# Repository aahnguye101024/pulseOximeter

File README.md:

# pulseOximeter
This board attempts to use the MAX86150 to in a small board to receive PPG, EKG, SPO2, and Heart Rate information. It features an nrf52832, some basic ui leds, and a power system capable of running off of and charging a lipo battery

# Board Pictures

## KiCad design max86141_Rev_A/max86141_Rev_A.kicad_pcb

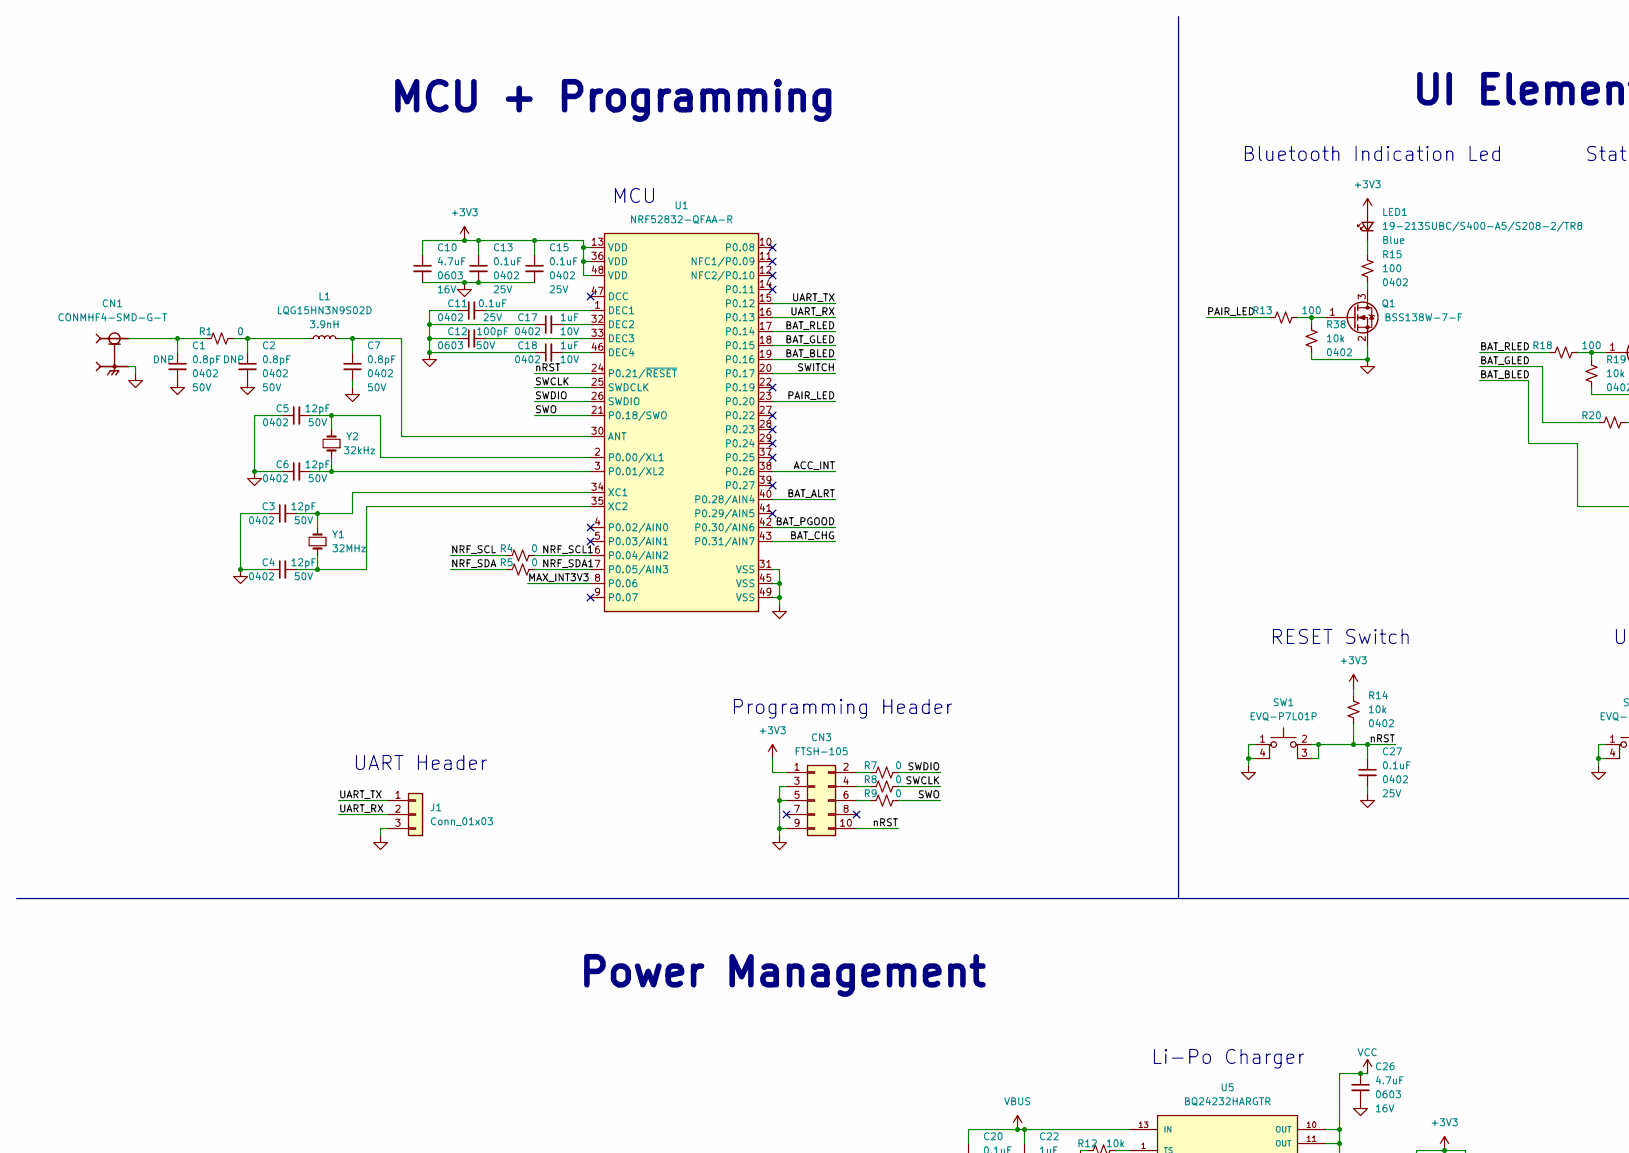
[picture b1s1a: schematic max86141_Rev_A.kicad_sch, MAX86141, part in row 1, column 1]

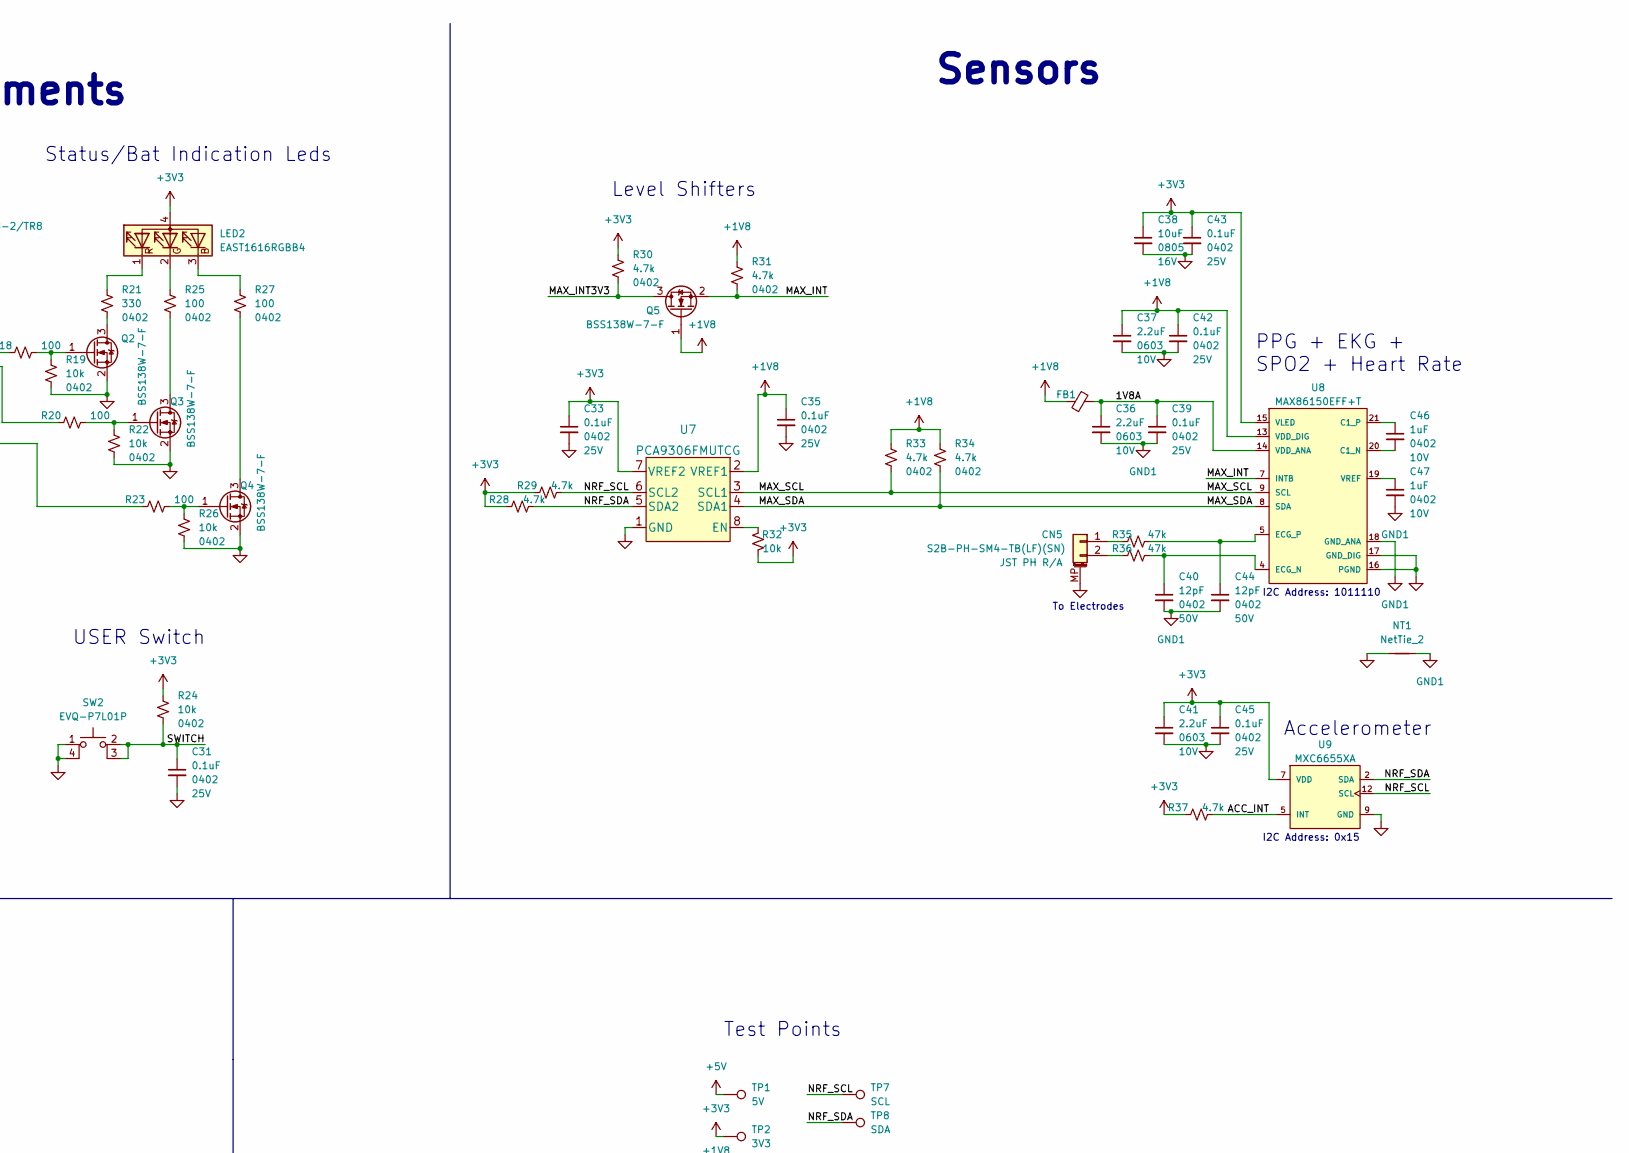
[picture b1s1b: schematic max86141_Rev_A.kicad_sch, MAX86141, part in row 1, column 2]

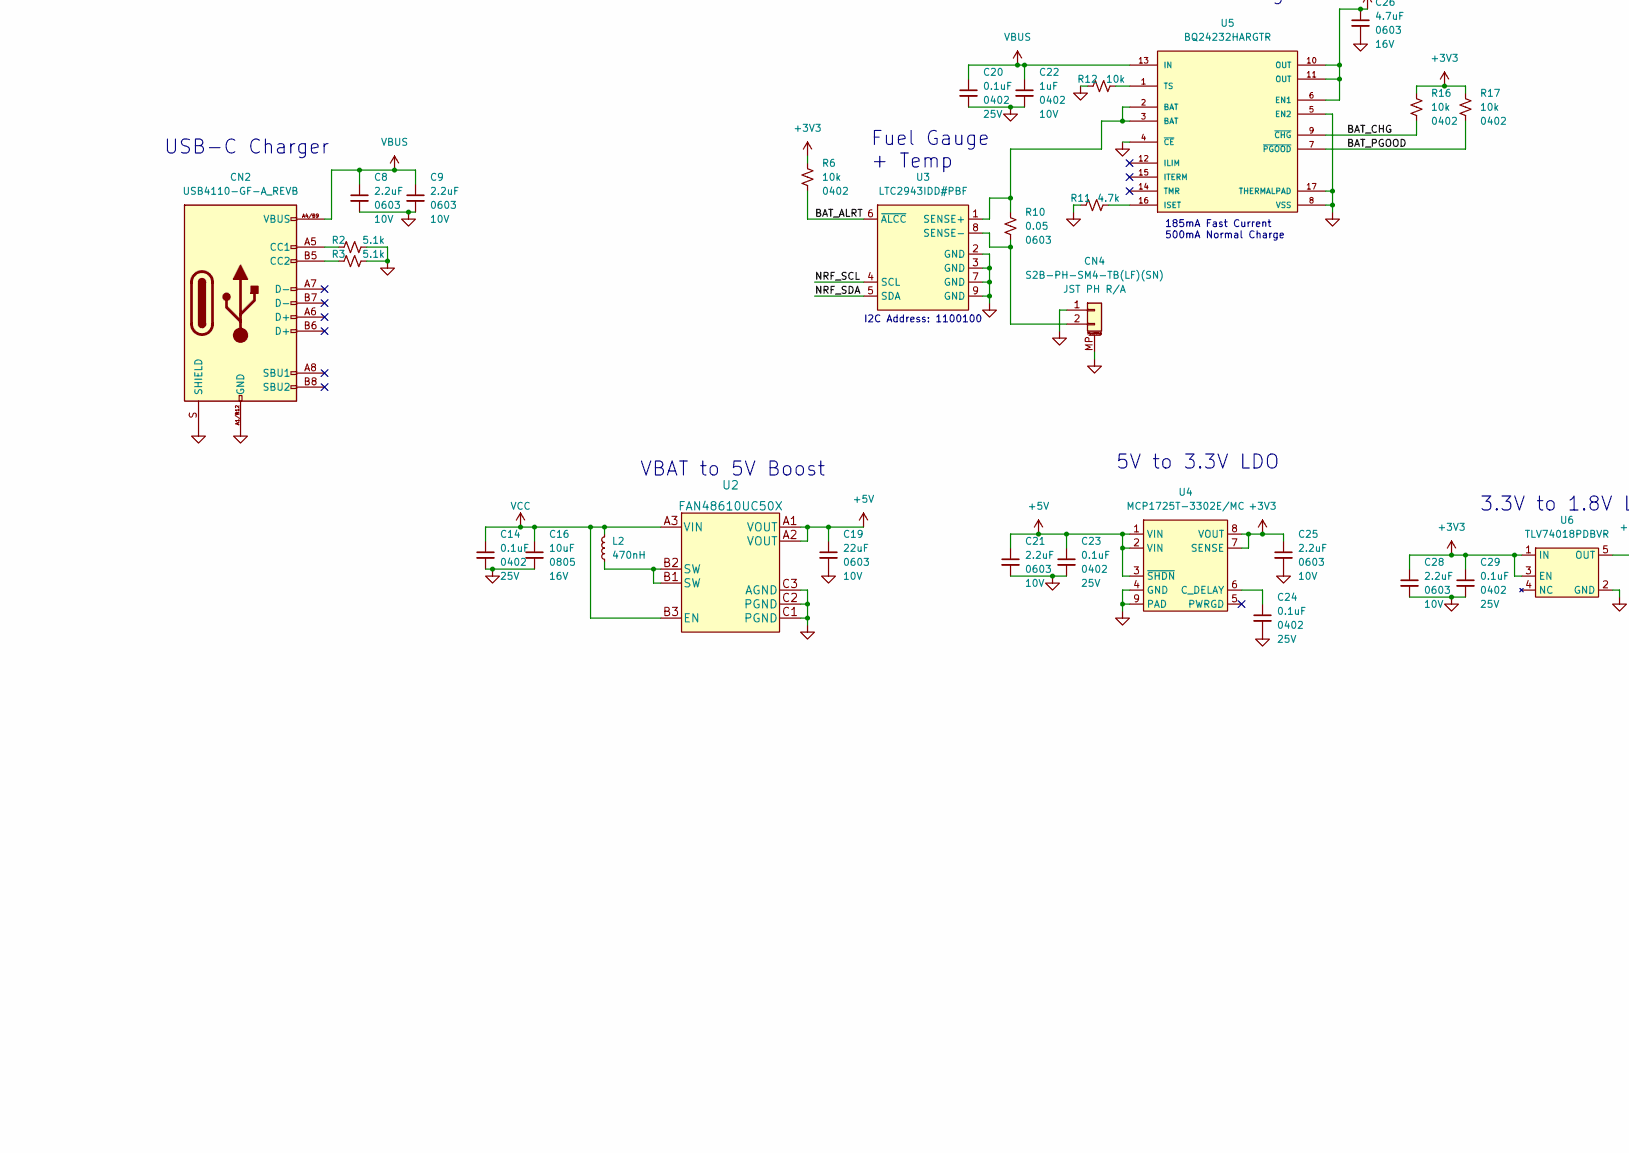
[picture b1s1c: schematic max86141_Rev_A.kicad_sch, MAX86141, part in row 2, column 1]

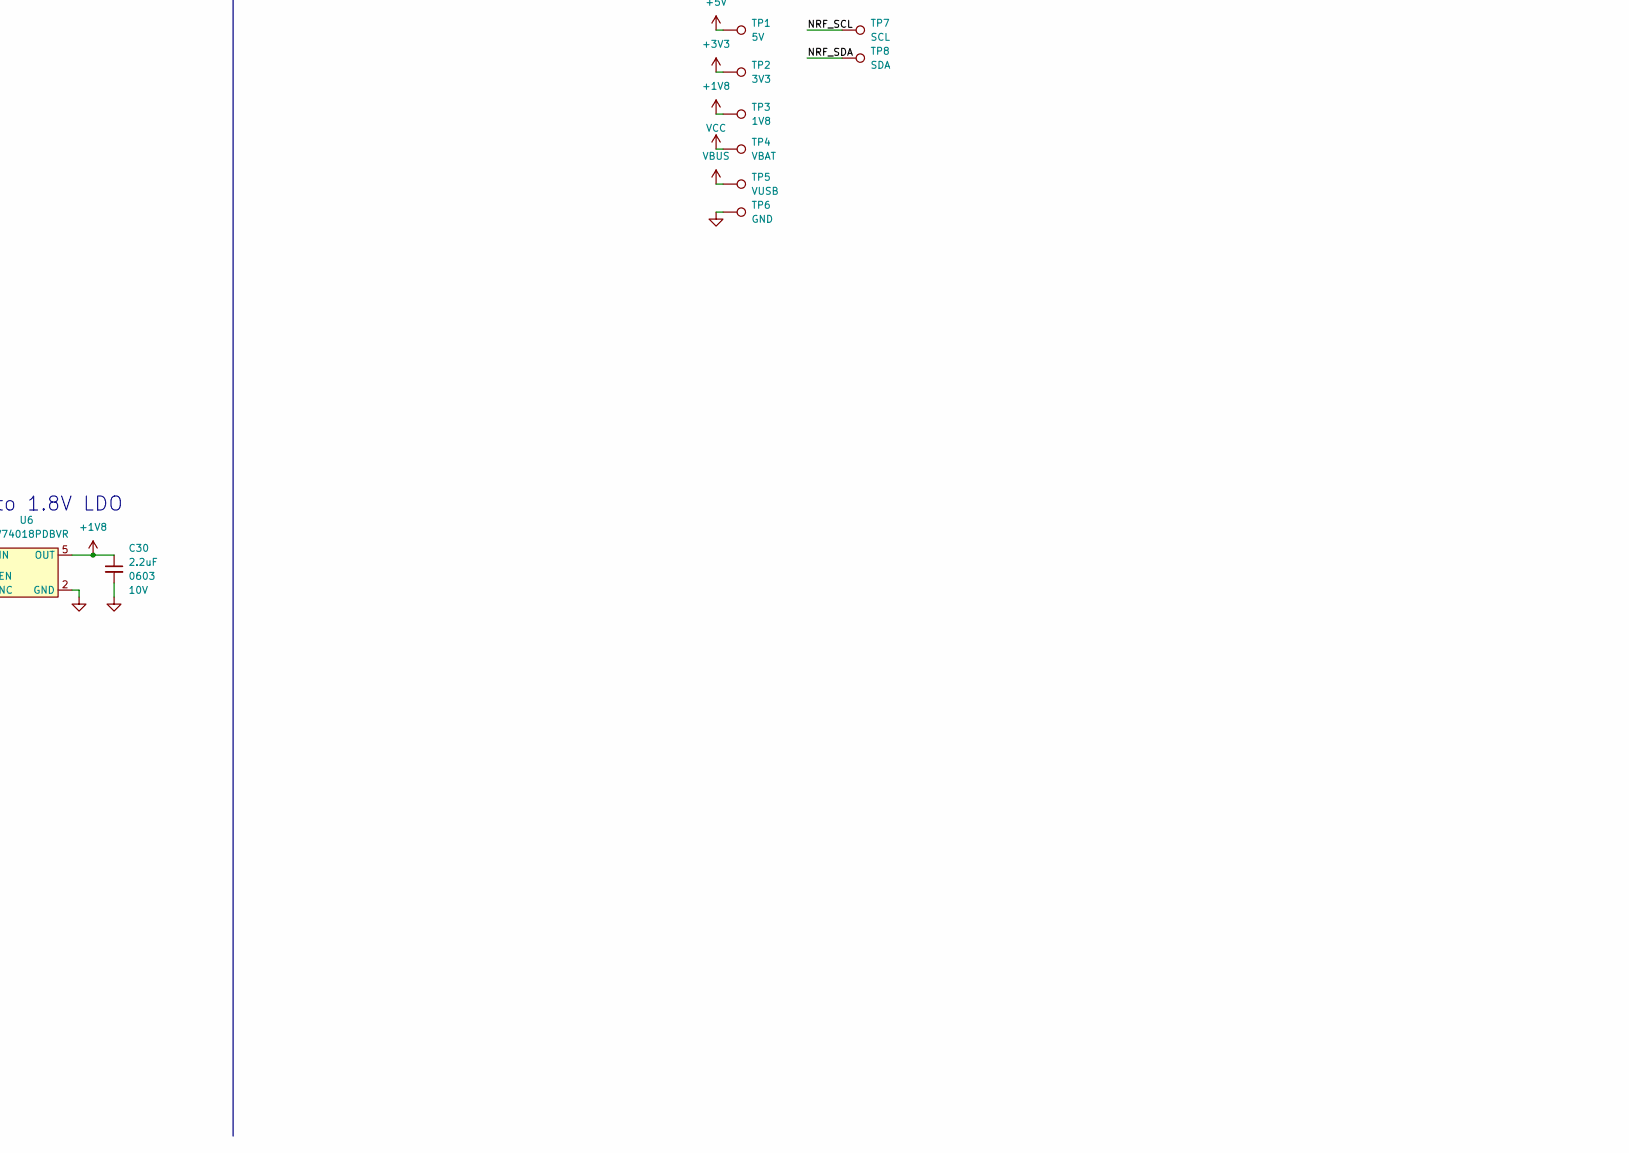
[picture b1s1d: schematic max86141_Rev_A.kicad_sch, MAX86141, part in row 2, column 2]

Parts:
C1, C2, C7: 0.8pF; C_0402_1005Metric; Voltage 50V; Part Number 311-3711-1-ND
C3, C4, C5, C6, C40, C44: 12pF; C_0402_1005Metric; Voltage 50V; Part Number 311-1641-1-ND
C8, C9, C21, C25, C28, C30, C36, C37, C41: 2.2uF; C_0603_1608Metric; Voltage 10V; Part Number 1276-1085-1-ND; JLCPCB Yes
C10, C26: 4.7uF; C_0603_1608Metric; Voltage 16V; Part Number 1276-1784-1-ND
C11, C13, C14, C15, C20, C23, C24, C27, C29, C31, C33, C35, C39, C42, C43, C45: 0.1uF; C_0402_1005Metric; Voltage 25V; Part Number 1276-1043-1-ND; JLCPCB Yes
C12: 100pF; C_0603_1608Metric; Voltage 50V; Part Number 399-C0603C101M5GAC7867CT-ND
C16, C38: 10uF; C_0805_2012Metric; Voltage 16V; Part Number 1276-2893-1-ND; JLCPCB Yes
C17, C18, C22, C46, C47: 1uF; C_0402_1005Metric; Voltage 10V; Part Number 1276-1076-1-ND; JLCPCB Yes
C19: 22uF; C_0603_1608Metric; Voltage 10V; Part Number 1276-1274-1-ND
CN1: CONMHF4-SMD-G-T; LINX_CONMHF4-SMD-G-T; Part Number 343-CONMHF4-SMD-G-TCT-ND
CN2: USB4110-GF-A_REVB; GCT_USB4110-GF-A_REVB; Part Number 2073-USB4110-GF-A-1-ND
CN3: FTSH-105; SAMTEC_FTSH-105-01-F-DV-P-TR; Part Number Personal
CN4, CN5: S2B-PH-SM4-TB(LF)(SN); JST_S2B-PH-SM4-TB(LF)(SN); Part Number 455-1749-1-ND
FB1: BLM15PX601SN1D; L_0402_1005Metric; Part Number 490-9657-1-ND
J1: Conn_01x03; PinHeader_1x03_P2.54mm_Vertical
L1: LQG15HN3N9S02D; L_0402_1005Metric; Part Number 490-1079-1-ND
L2: MBKK1608TR47N; L_0603_1608Metric; Part Number 587-4154-1-ND
LED1: 19-213SUBC/S400-A5/S208-2/TR8; LED_0603_1608Metric; Part Number 1080-1581-1-ND; JLCPCB Yes
LED2: EAST1616RGBB4; Part Number 1080-1552-1-ND
NT1: NetTie_2; NetTie-2_SMD_Pad2.0mm
Q1, Q2, Q3, Q4, Q5: BSS138W-7-F; SOT-323_SC-70; Part Number BSS138W-FDICT-ND
R1, R4, R5, R7, R8, R9: 0; R_0402_1005Metric; Part Number RMCF0402ZT0R00CT-ND; JLCPCB Yes
R2, R3: 5.1k; R_0402_1005Metric; Part Number 311-5.10KLRCT-ND
R6, R12, R14, R16, R17, R19, R22, R24, R26, R32, R38: 10k; R_0402_1005Metric; Part Number RMCF0402FT10K0CT-ND; JLCPCB Yes
R10: 0.05; R_0603_1608Metric; Part Number 273-KDV06FR050ETCT-ND
R11, R28, R29, R30, R31, R33, R34, R37: 4.7k; R_0402_1005Metric; Part Number RMCF0402FT4K70CT-ND; JLCPCB Yes
R13, R15, R18, R20, R23, R25, R27: 100; R_0402_1005Metric; Part Number RMCF0402FT100RCT-ND; JLCPCB Yes
R21: 330; R_0402_1005Metric; Part Number 311-330LRCT-ND
R35, R36: 47k; R_0402_1005Metric; Part Number RMCF0402FT47K0CT-ND
SW1, SW2: EVQ-P7L01P; SW_EVQ-P7L01P; Part Number P16769CT-ND
TP1: 5V; TestPoint_Pad_D1.0mm
TP2: 3V3; TestPoint_Pad_D1.0mm
TP3: 1V8; TestPoint_Pad_D1.0mm
TP4: VBAT; TestPoint_Pad_D1.0mm
TP5: VUSB; TestPoint_Pad_D1.0mm
TP6: GND; TestPoint_Pad_D1.0mm
TP7: SCL; TestPoint_Pad_D1.0mm
TP8: SDA; TestPoint_Pad_D1.0mm
U1: NRF52832-QFAA-R; QFN-48-1EP_6x6mm_P0.4mm_EP4.6x4.6mm; Part Number Personal; JLCPCB Yes
U2: FAN48610UC50X; Part Number FAN48610UC50XCT-ND
U3: LTC2943IDD#PBF; DFN-8-1EP_3x3mm_P0.5mm_EP1.66x2.38mm; Part Number Personal
U4: MCP1725T-3302E/MC; MCP1725T-3302E; Part Number Personal
U5: BQ24232HARGTR; QFN50P300X300X100-17N; Part Number Personal
U6: TLV74018PDBVR; SOT-23-5; Part Number 296-TLV74018PDBVRCT-ND
U7: PCA9306FMUTCG; Part Number PCA9306FMUTCGOSCT-ND
U8: MAX86150EFF+T; XDCR_MAX86150EFF+; Part Number MAX86150EFF+TCT-ND
U9: MXC6655XA; IC_MXC6655XA; Part Number 1267-MXC6655XACT-ND
Y1: XRCGB32M000F2P01R0; OSC_XRCGB32M000F2P01R0; Part Number 490-18340-1-ND
Y2: CM8V-T1A-32.768KHZ-9PF-20PPM-TA-QC; XTAL_CM8V-T1A-32.768KHZ-9PF-20PPM-TA-QC; Part Number 2195-CM8V-T1A-32.768KHZ-9PF-20PPM-TA-QC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

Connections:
+1V8: C30.1, C35.1, C37.1, C42.1, FB1.1, Q5.1 (G), R31.1, R33.1, R34.1, TP3.1, U6.5 (OUT), U7.2 (VREF1), U8.13 (VDD_DIG)
+3V3: C10.1, C13.1, C15.1, C25.1, C28.1, C29.1, C33.1, C38.1, C41.1, C43.1, C45.1, CN3.1, LED1.2 (A), LED2.4 (A), R6.1, R14.1, R16.1, R17.1, R24.1, R28.1, R29.1, R30.1, R32.2, R37.1, TP2.1, U1.13 (VDD), U1.36 (VDD), U1.48 (VDD), U4.7 (SENSE), U4.8 (VOUT), U6.1 (IN), U6.3 (EN), U7.7 (VREF2), U8.15 (VLED), U9.7 (VDD)
+5V: C19.1, C21.1, C23.1, TP1.1, U2.A1 (VOUT), U2.A2 (VOUT), U4.1 (VIN), U4.2 (VIN), U4.3 (~SHDN)
/1V8A: C36.1, C39.1, FB1.2, U8.14 (VDD_ANA)
/ACC_INT: R37.2, U1.38 (P0.26), U9.5 (INT)
/BAT_ALRT: R6.2, U1.40 (P0.28/AIN4), U3.6 (~ALCC)
/BAT_BLED: R23.1, U1.19 (P0.16)
/BAT_CHG: R16.2, U1.43 (P0.31/AIN7), U5.9 (~CHG)
/BAT_GLED: R20.1, U1.18 (P0.15)
/BAT_PGOOD: R17.2, U1.42 (P0.30/AIN6), U5.7 (~PGOOD)
/BAT_RLED: R18.1, U1.17 (P0.14)
/MAX_INT: Q5.2 (S), R31.2, U8.7 (INTB)
/MAX_INT3V3: Q5.3 (D), R30.2, U1.8 (P0.06)
/MAX_SCL: R33.2, U7.3 (SCL1), U8.9 (SCL)
/MAX_SDA: R34.2, U7.4 (SDA1), U8.8 (SDA)
/NRF_SCL: R4.1, R29.2, TP7.1, U3.4 (SCL), U7.6 (SCL2), U9.12 (SCL)
/NRF_SCL1: R4.2, U1.6 (P0.04/AIN2)
/NRF_SDA: R5.1, R28.2, TP8.1, U3.5 (SDA), U7.5 (SDA2), U9.2 (SDA)
/NRF_SDA1: R5.2, U1.7 (P0.05/AIN3)
/PAIR_LED: R13.1, U1.23 (P0.20)
/SWCLK: R8.2, U1.25 (SWDCLK)
/SWDIO: R7.2, U1.26 (SWDIO)
/SWITCH: C31.1, R24.2, SW2.2, SW2.3 (K), U1.20 (P0.17)
/SWO: R9.2, U1.21 (P0.18/SWO)
/UART_RX: J1.2, U1.16 (P0.13)
/UART_TX: J1.1, U1.15 (P0.12)
/nRST: C27.1, CN3.10, R14.2, SW1.2, SW1.3 (K), U1.24 (P0.21/~RESET)
GND: C1.2, C2.2, C3.1, C4.1, C5.1, C6.1, C7.2, C8.2, C9.2, C10.2, C11.1, C12.1, C13.2, C14.2, C15.2, C16.2, C17.1, C18.1, C19.2, C20.2, C21.2, C22.2, C23.2, C24.2, C25.2, C26.2, C27.2, C28.2, C29.2, C30.2, C31.2, C33.2, C35.2, C37.2, C38.2, C41.2, C42.2, C43.2, C45.2, CN1.S1, CN1.S2, CN1.S3, CN2.A1/B12 (GND), CN2.B1/A12 (GND), CN2.S (SHIELD), CN3.3, CN3.5, CN3.9, CN4.1, CN4.MP (MountPin), CN5.MP (MountPin), J1.3, NT1.1, Q1.2 (S), Q2.2 (S), Q3.2 (S), Q4.2 (S), R2.2, R3.2, R11.1, R12.1, R19.2, R22.2, R26.2, R38.2, SW1.1, SW1.4 (A), SW2.1, SW2.4 (A), TP6.1, U1.31 (VSS), U1.45 (VSS), U1.49 (VSS), U2.C1 (PGND), U2.C2 (PGND), U2.C3 (AGND), U3.2 (GND), U3.3 (GND), U3.7 (GND), U3.9 (GND), U4.4 (GND), U4.9 (PAD), U5.4 (~CE), U5.5 (EN2), U5.8 (VSS), U5.17 (THERMALPAD), U6.2 (GND), U7.1 (GND), U8.16 (PGND), U8.17 (GND_DIG), U9.9 (GND)
GND1: C36.2, C39.2, C40.2, C44.2, C47.2, NT1.2, U8.18 (GND_ANA)
unnamed: C1.1, CN1.1, R1.1
unnamed: C2.1, L1.1, R1.2
unnamed: C3.2, U1.34 (XC1), Y1.3 (2)
unnamed: C4.2, U1.35 (XC2), Y1.1
unnamed: C5.2, U1.2 (P0.00/XL1), Y2.2
unnamed: C6.2, U1.3 (P0.01/XL2), Y2.1
unnamed: C7.1, L1.2, U1.30 (ANT)
unnamed: C11.2, U1.1 (DEC1)
unnamed: C12.2, U1.33 (DEC3)
unnamed: C17.2, U1.32 (DEC2)
unnamed: C18.2, U1.46 (DEC4)
unnamed: C24.1, U4.6 (C_DELAY)
unnamed: C40.1, R36.2, U8.4 (ECG_N)
unnamed: C44.1, R35.2, U8.5 (ECG_P)
unnamed: C46.1, U8.21 (C1_P)
unnamed: C46.2, U8.20 (C1_N)
unnamed: C47.1, U8.19 (VREF)
unnamed: CN2.A5 (CC1), R2.1
unnamed: CN2.B5 (CC2), R3.1
unnamed: CN3.2, R7.1
unnamed: CN3.4, R8.1
unnamed: CN3.6, R9.1
unnamed: CN4.2, R10.2, U3.8 (SENSE-)
unnamed: CN5.1, R35.1
unnamed: CN5.2, R36.1
unnamed: L2.1, U2.B1 (SW), U2.B2 (SW)
unnamed: LED1.1 (K), R15.1
unnamed: LED2.1 (RK), R21.1
unnamed: LED2.2 (GK), R25.1
unnamed: LED2.3 (BK), R27.1
unnamed: Q1.1 (G), R13.2, R38.1
unnamed: Q1.3 (D), R15.2
unnamed: Q2.1 (G), R18.2, R19.1
unnamed: Q2.3 (D), R21.2
unnamed: Q3.1 (G), R20.2, R22.1
unnamed: Q3.3 (D), R25.2
unnamed: Q4.1 (G), R23.2, R26.1
unnamed: Q4.3 (D), R27.2
unnamed: R10.1, U3.1 (SENSE+), U5.2 (BAT), U5.3 (BAT)
unnamed: R11.2, U5.16 (ISET)
unnamed: R12.2, U5.1 (TS)
unnamed: R32.1, U7.8 (EN)
VBUS: C8.1, C9.1, C20.1, C22.1, CN2.A4/B9 (VBUS), CN2.B4/A9 (VBUS), TP5.1, U5.13 (IN)
VCC: C14.1, C16.1, C26.1, L2.2, TP4.1, U2.A3 (VIN), U2.B3 (EN), U5.6 (EN1), U5.10 (OUT), U5.11 (OUT)

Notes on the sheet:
VBAT to 5V Boost
To Electrodes
PPG + EKG + SPO2 + Heart Rate
Fuel Gauge + Temp
Level Shifters
185mA Fast Current 500mA Normal Charge
3.3V to 1.8V LDO
UART Header
USB-C Charger
Test Points
Li-Po Charger
UI Elements
5V to 3.3V LDO
MCU + Programming
I2C Address: 1100100
Power Management
I2C Address: 0x15
I2C Address: 1011110
Programming Header
Sensors
Accelerometer
Bluetooth Indication Led
USER Switch
RESET Switch
MCU
Status/Bat Indication Leds

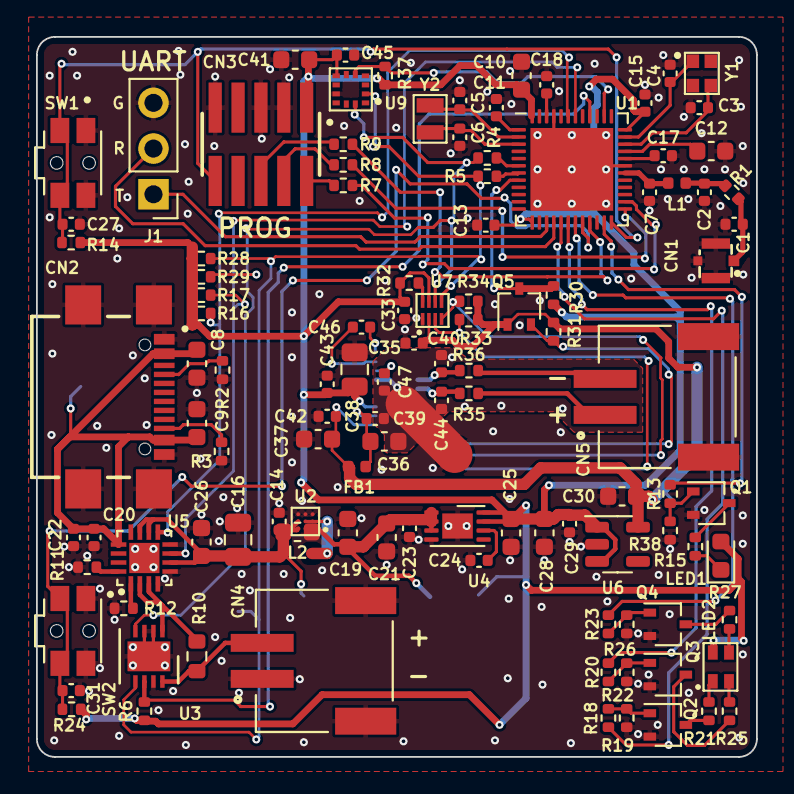
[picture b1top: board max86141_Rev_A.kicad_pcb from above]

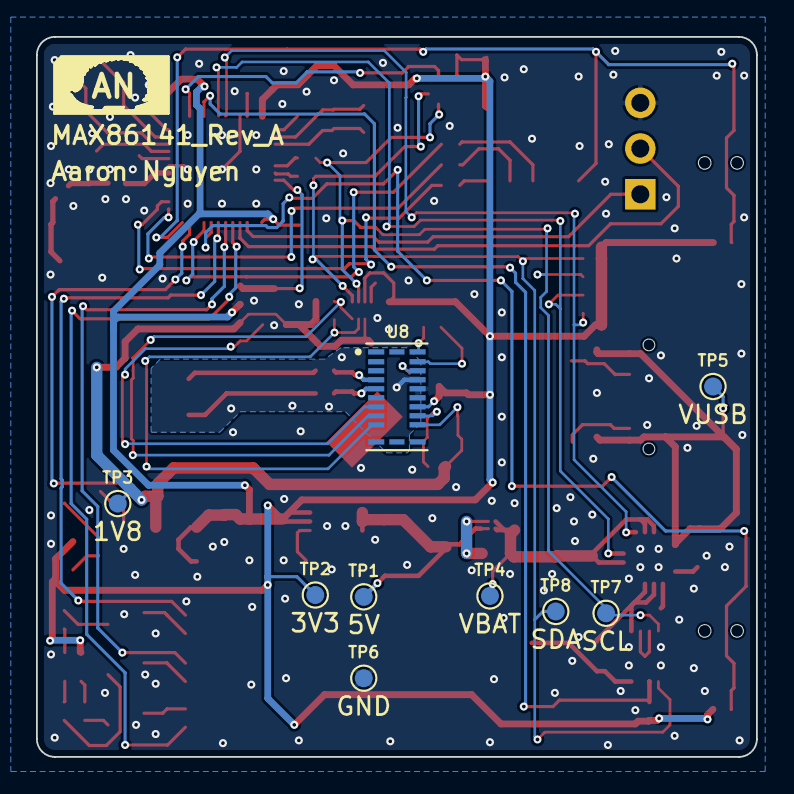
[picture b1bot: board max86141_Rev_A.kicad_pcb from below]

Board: 4 copper layers, 40.0 x 40.0 mm, 121 parts (9 on the bottom side), 73 nets.

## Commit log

2024-01-31 initial push
2024-01-31 Updated read me
